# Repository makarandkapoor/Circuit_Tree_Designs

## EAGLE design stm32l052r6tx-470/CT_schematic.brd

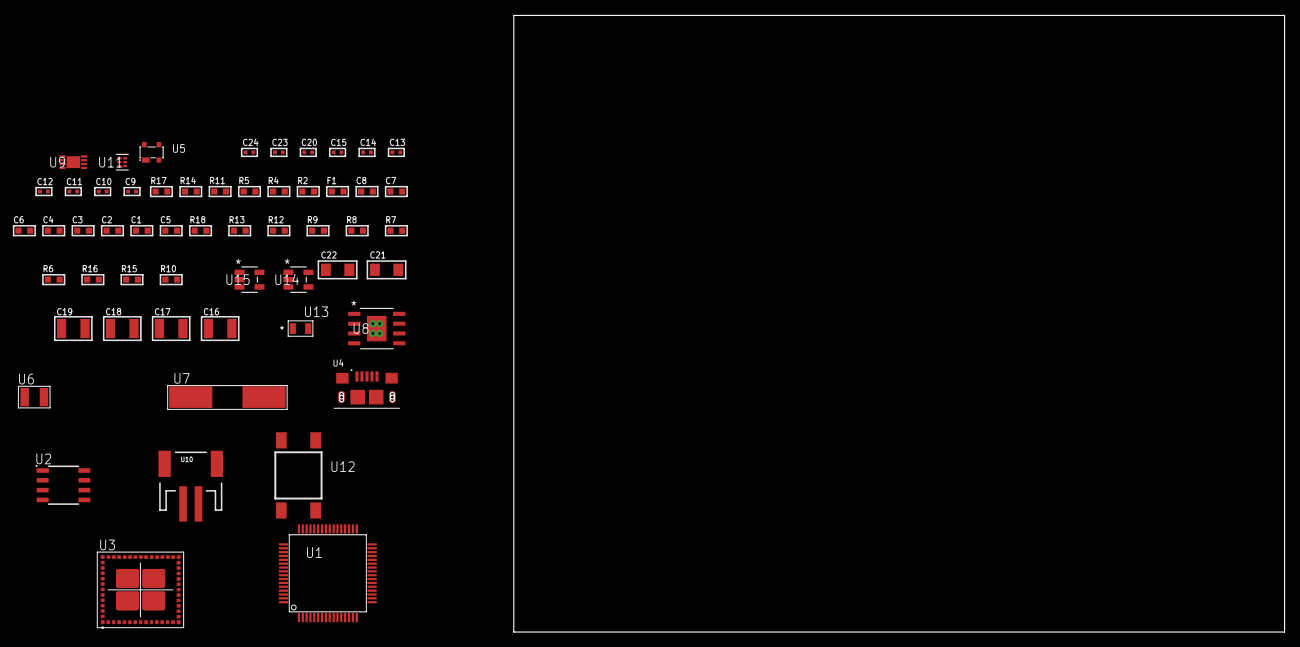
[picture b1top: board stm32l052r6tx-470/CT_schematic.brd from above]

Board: 2 copper layers, 122.6 x 80.0 mm, 56 parts (0 on the bottom side), 32 nets, no tracks yet.

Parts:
C1, C2, C3, C4, C8: 1e-07; C0603
C5: 4.7e-06; C0603
C6: 1e-08; C0603
C7: 1e-06; C0603
C9, C10, C11, C12: 1e-11; C0402
C13, C23, C24: 1e-08; C0402
C14, C15, C20: 1e-07; C0402
C16, C17, C18, C19: 1e-05; C1210
C21, C22: 1e-05; C1206
F1: 240.0; L0603
R2: 1000.0; R0603
R4, R5: 4700.0; R0603
R6, R7, R8, R9, R12, R13, R18: 10000.0; R0603
R10: 4031.5447154472; R0603
R11: 2200.0; R0603
R14: 9100.0; R0603
R15: 680000.0; R0603
R16: 120000.0; R0603
R17: 2000.0; R0603
U1: STM32L052R6T6; LQFP64
U2: AT25640B-SSHL-T; SOIC-8
U3: MBH7BLZ02-109004
U4: 10118193-0001LF; FCI_10118193-0001LF
U5: prtr5v0u2ax; SOT143B
U6: ABS07-32.768KHZ-7-T
U7: ABLS-25.000MHZ-B2F-T
U8: MIC5234YME; SOIC-8_EP
U9: MCP73831T-2ACI/MC; DFN8_2X3MC
U10: S2B-PH-SM4-TB(LF)(SN); JST-2-SMD
U11: TPS3895ADRYR; SON-6
U12: 4-1437565-2; SW_4-1437565-2
U13: Q65110A2395; LGM67K-G1J2-24-Z
U14, U15: nc7sz125m5x; NC7SZ125M5X

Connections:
CLK_CRYSTAL_U1_3: C9.1, U1.3, U6.1
CLK_CRYSTAL_U1_4: C10.1, U1.4, U6.2
CLK_CRYSTAL_U1_5: C11.1, U1.5, U7.1
CLK_CRYSTAL_U1_6: C12.1, U1.6, U7.2
GND: C1.2, C2.2, C3.2, C4.2, C5.2, C6.2, C7.2, C8.2, C9.2, C10.2, C11.2, C12.2, C13.2, C14.2, C15.2, C16.2, C17.2, C18.2, C19.2, C20.2, C21.2, C22.2, C23.2, C24.2, R2.2, R6.2, R11.2, R14.2, R16.2, R17.2, U1.12, U1.18, U1.31, U1.47, U1.63, U2.4, U3.1, U3.3, U3.15, U3.27, U3.29, U3.41, U3.42, U3.43, U3.44, U3.45, U3.46, U3.47, U3.48, U3.49, U3.50, U3.52, U3.53, U3.54, U3.55, U3.56, U4.5, U4.6, U4.7, U4.8, U4.9, U5.1, U8.7, U8.EPAD, U9.6, U9.9, U10.2, U11.2, U13.C, U14.1, U14.3, U15.1, U15.3
INPUT_USBPOWER_5V: C21.1, R18.2, U4.1, U5.4, U9.1, U9.2
NET_U1_7: R5.1, U1.7, U15.4
NET_U1_13: C6.1, C7.1, F1.1, U1.13
NET_U1_60: R6.1, U1.60
NET_U1_62: U12.3, U12.4
NET_U2_3: R7.1, U2.3
NET_U2_7: R9.1, U2.7
NET_U3_39: R4.1, U3.39, U14.4
NET_U8_4: R10.2, R11.1, U8.4
NET_U9_5: R18.1, U9.5
NET_U9_8: R17.1, U9.8
NET_U11_1: R13.1, R14.1, U11.1
NET_U11_3: R15.2, R16.1, U11.3
NET_U11_4: R12.1, U11.4, U14.2, U15.2
NET_U12_1: R2.1, U12.1, U12.2
PROC_LPUART1_CTS: U1.22, U3.26
PROC_LPUART1_RTS: U1.27, U3.24
PROC_LPUART1_RX: U1.25, U3.25
PROC_LPUART1_TX: U1.24, U3.23
PROC_SPI1_MISO: U1.56, U2.2
PROC_SPI1_MOSI: U1.23, U2.5
PROC_SPI1_NSS: R8.1, U1.20, U2.1
PROC_SPI1_SCK: U1.21, U2.6
PROC_USB_DM: U4.2, U5.3
PROC_USB_DP: U4.3, U5.2
VCC_S1_3V7: C16.1, C17.1, C22.1, U8.5, U8.8, U9.3, U9.4, U10.1
VCC_TIER1_3V3: C1.1, C2.1, C3.1, C4.1, C5.1, C8.1, C13.1, C14.1, C15.1, C18.1, C19.1, C20.1, C23.1, C24.1, F1.2, R4.2, R5.2, R7.2, R8.2, R9.2, R10.1, R12.2, R13.2, R15.1, U1.1, U1.19, U1.32, U1.48, U1.64, U2.8, U3.28, U8.1, U11.6, U14.5, U15.5

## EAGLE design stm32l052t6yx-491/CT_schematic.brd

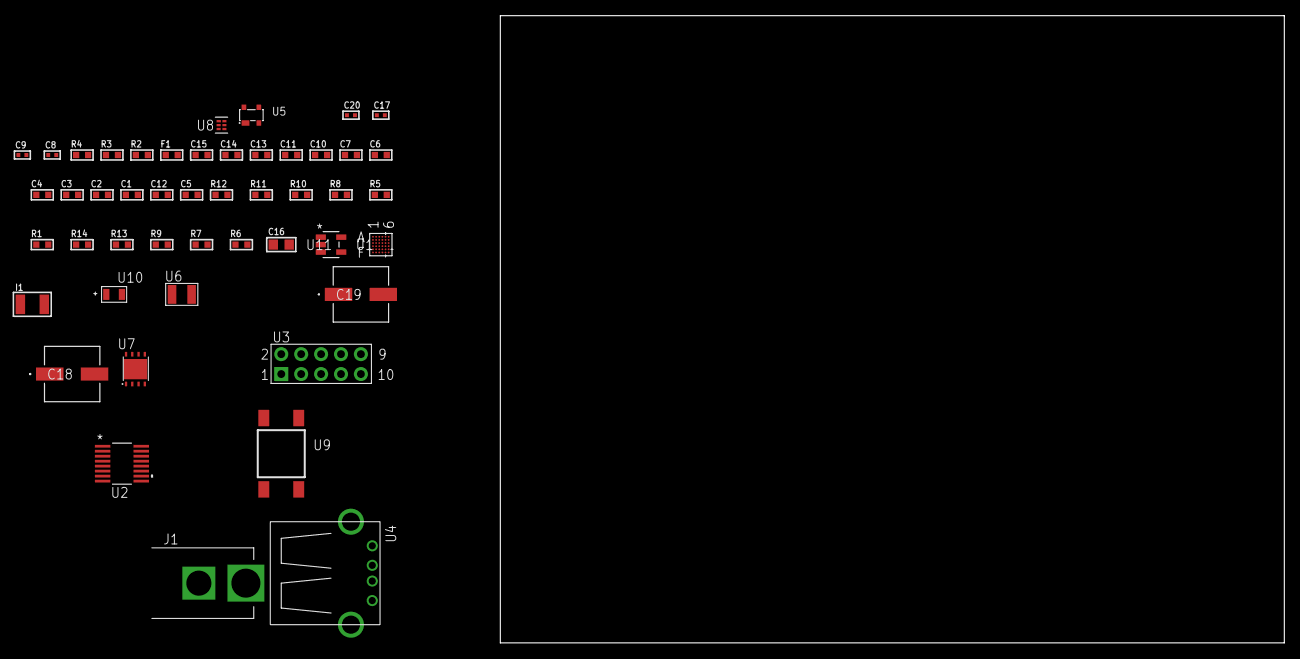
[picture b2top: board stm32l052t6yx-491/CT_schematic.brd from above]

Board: 2 copper layers, 100.0 x 80.0 mm, 48 parts (0 on the bottom side), 32 nets, no tracks yet.

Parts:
C1, C2, C3, C4: 1e-07; C0603
C5: 4.7e-06; C0603
C6: 1e-08; C0603
C7, C10, C11, C13, C14: 1e-06; C0603
C8, C9: 1e-11; C0402
C12: 2.2e-07; C0603
C15: 8e-07; R0603
C16: 1e-05; C0805
C17: 1e-07; C0402
C18, C19: 0.0001; EXV-9H
C20: 1e-08; C0402
F1: 240.0; L0603
I1: 1e-05; L1210
J1: PJ-037B; PJ-037B_PACKAGE
R1, R5, R10, R11: 10000.0; R0603
R2: 1000.0; R0603
R3: 910.0; R0603
R4: 4700.0; R0603
R6, R7, R9: 100000.0; R0603
R8: 36000.0; R0603
R12: 82000.0; R0603
R13: 300000.0; R0603
R14: 120000.0; R0603
U1: STM32L052T6Y6TR; WLCSP36
U2: LTC2804CGN-1#PBF; SSOP-16
U3: HTSS-105-01-G-D
U4: 61400416021; USB-A-H
U5: prtr5v0u2ax; SOT143B
U6: ABS07-32.768KHZ-7-T
U7: LP2951ACSDX/NOPB; WSON-8
U8: TPS3895ADRYR; SON-6
U9: 4-1437565-2; SW_4-1437565-2
U10: Q65110A2395; LGM67K-G1J2-24-Z
U11: nc7sz125m5x; NC7SZ125M5X

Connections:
CLK_CRYSTAL_U1_A6: C8.1, U1.A6, U6.1
CLK_CRYSTAL_U1_B6: C9.1, U1.B6, U6.2
GND: C1.2, C2.2, C3.2, C4.2, C5.2, C6.2, C7.2, C8.2, C9.2, C10.2, C11.2, C13.2, C14.2, C15.2, C16.2, C17.2, C18.2, C19.2, C20.2, J1.2, R2.2, R5.2, R9.2, R12.2, R14.2, U1.D6, U2.8, U3.9, U4.4, U4.5, U4.6, U5.1, U7.3, U7.4, U7.PAD, U8.2, U10.C, U11.1, U11.3
NET_U1_C5: R5.1, U1.C5
NET_U1_C6: R4.1, U1.C6, U11.4
NET_U1_D5: C6.1, C7.1, F1.1, U1.D5, U1.E6
NET_U1_F5: R3.1, U1.F5, U10.A
NET_U1_F6: R1.1, U1.F6, U9.3, U9.4
NET_U2_6: C10.1, U2.6
NET_U2_7: C12.1, I1.2, U2.7
NET_U2_9: C11.1, U2.9
NET_U2_10: C12.2, U2.10
NET_U2_11: R6.1, U2.11
NET_U3_3: U2.1, U3.3
NET_U3_4: U2.2, U3.4
NET_U3_5: U2.3, U3.5
NET_U3_6: U2.4, U3.6
NET_U5_4: U4.1, U5.4
NET_U7_5: R7.1, U7.5
NET_U7_7: R8.2, R9.1, U7.7
NET_U8_1: R11.1, R12.1, U8.1
NET_U8_3: R13.2, R14.1, U8.3
NET_U8_4: R10.1, U8.4, U11.2
NET_U9_1: R2.1, U9.1, U9.2
PROC_LPUART1_CTS: U1.E3, U2.13
PROC_LPUART1_RTS: U1.C3, U2.15
PROC_LPUART1_RX: U1.D2, U2.16
PROC_LPUART1_TX: U1.E2, U2.14
PROC_USB_DM: U1.C2, U4.2, U5.3
PROC_USB_DP: U1.B1, U4.3, U5.2
VCC_S1_11V7: C15.1, C18.1, C19.1, J1.1, U7.8
VCC_TIER1_1V8: C1.1, C2.1, C3.1, C4.1, C5.1, C13.1, C14.1, C16.1, C17.1, C20.1, F1.2, I1.1, R1.2, R3.2, R4.2, R6.2, R7.2, R8.1, R10.2, R11.2, R13.1, U1.A5, U1.F1, U2.5, U2.12, U7.1, U8.6, U11.5

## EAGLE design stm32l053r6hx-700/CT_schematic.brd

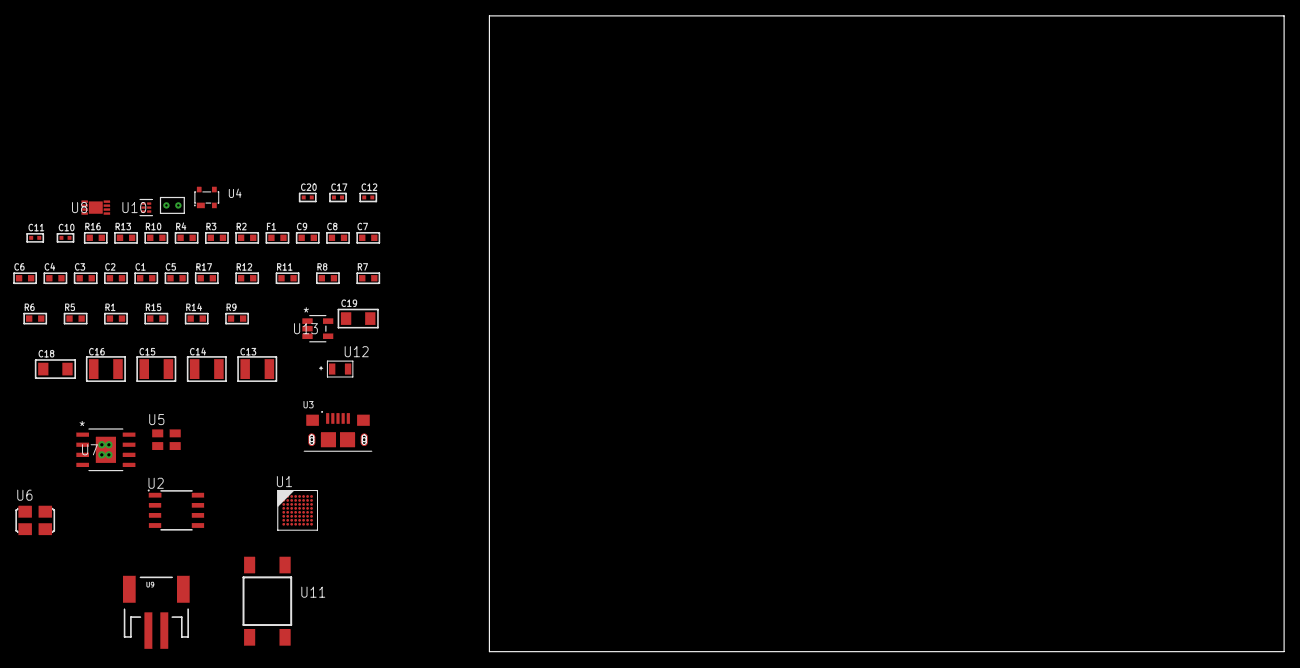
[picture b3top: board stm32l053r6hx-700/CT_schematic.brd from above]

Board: 2 copper layers, 122.6 x 80.0 mm, 52 parts (0 on the bottom side), 28 nets, no tracks yet.

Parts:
C1, C2, C3, C4, C6, C9: 1e-07; C0603
C5: 4.7e-06; C0603
C7: 1e-08; C0603
C8: 1e-06; C0603
C10, C11, C12, C20: 1e-08; C0402
C13, C14, C15, C16: 1e-05; C1210
C17: 1e-07; C0402
C18, C19: 1e-05; C1206
F1: 240.0; L0603
R1, R5, R6, R7, R8, R11, R12, R17: 10000.0; R0603
R2: 1000.0; R0603
R3: 1600.5; R0603
R4: 4700.0; R0603
R9: 4031.5447154472; R0603
R10: 2200.0; R0603
R13: 9100.0; R0603
R14: 680000.0; R0603
R15: 120000.0; R0603
R16: 2000.0; R0603
U1: STM32L053R6H6; TFBGA64
U2: AT25010B-SSHL-T; SOIC-8
U3: 10118193-0001LF; FCI_10118193-0001LF
U4: prtr5v0u2ax; SOT143B
U5: ASEK-32.768KHz-ECST; ASEK
U6: ASFL1-25MHZ-NCS; ASFL1
U7: MIC5234YME; SOIC-8_EP
U8: MCP73831T-2ACI/MC; DFN8_2X3MC
U9: S2B-PH-SM4-TB(LF)(SN); JST-2-SMD
U10: TPS3895ADRYR; SON-6
U11: 4-1437565-2; SW_4-1437565-2
U12: Q65110A2395; LGM67K-G1J2-24-Z
U13: nc7sz125m5x; NC7SZ125M5X
U14: Dummy; DUMMY_PACKAGE_116

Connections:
CLK_U1_A1: U1.A1, U5.3
CLK_U1_C1: U1.C1, U6.3
GND: C1.2, C2.2, C3.2, C4.2, C5.2, C6.2, C7.2, C8.2, C9.2, C10.2, C11.2, C12.2, C13.2, C14.2, C15.2, C16.2, C17.2, C18.2, C19.2, C20.2, R2.2, R5.2, R10.2, R13.2, R15.2, R16.2, U1.C2, U1.D4, U1.D5, U1.D6, U1.F1, U2.4, U3.5, U3.6, U3.7, U3.8, U3.9, U4.1, U5.2, U6.2, U7.7, U7.EPAD, U8.6, U8.9, U9.2, U10.2, U12.C, U13.1, U13.3, U14.1
INPUT_USBPOWER_5V: C18.1, R17.2, U3.1, U4.4, U8.1, U8.2
NET_U1_B2: C6.1, U1.B2
NET_U1_B4: R5.1, U1.B4
NET_U1_E1: R4.1, U1.E1, U13.4
NET_U1_H1: C7.1, C8.1, F1.1, U1.G1, U1.H1
NET_U1_H7: R3.1, U1.H7, U12.A
NET_U1_H8: R1.1, U1.H8, U11.3, U11.4
NET_U2_3: R6.1, U2.3
NET_U2_7: R8.1, U2.7
NET_U7_4: R9.2, R10.1, U7.4
NET_U8_5: R17.1, U8.5
NET_U8_8: R16.1, U8.8
NET_U10_1: R12.1, R13.1, U10.1
NET_U10_3: R14.2, R15.1, U10.3
NET_U10_4: R11.1, U10.4, U13.2
NET_U11_1: R2.1, U11.1, U11.2
PROC_DAC_OUT1: U1.H3, U14.2
PROC_SPI1_MISO: U1.A4, U2.2
PROC_SPI1_MOSI: U1.C4, U2.5
PROC_SPI1_NSS: R7.1, U1.A6, U2.1
PROC_SPI1_SCK: U1.A5, U2.6
PROC_USB_DM: U1.C8, U3.2, U4.3
PROC_USB_DP: U1.B8, U3.3, U4.2
VCC_S1_3V7: C13.1, C14.1, C19.1, U7.5, U7.8, U8.3, U8.4, U9.1
VCC_TIER1_3V3: C1.1, C2.1, C3.1, C4.1, C5.1, C9.1, C10.1, C11.1, C12.1, C15.1, C16.1, C17.1, C20.1, F1.2, R1.2, R3.2, R4.2, R6.2, R7.2, R8.2, R9.1, R11.2, R12.2, R14.1, U1.D2, U1.E4, U1.E5, U1.E6, U2.8, U5.4, U6.4, U7.1, U10.6, U13.5

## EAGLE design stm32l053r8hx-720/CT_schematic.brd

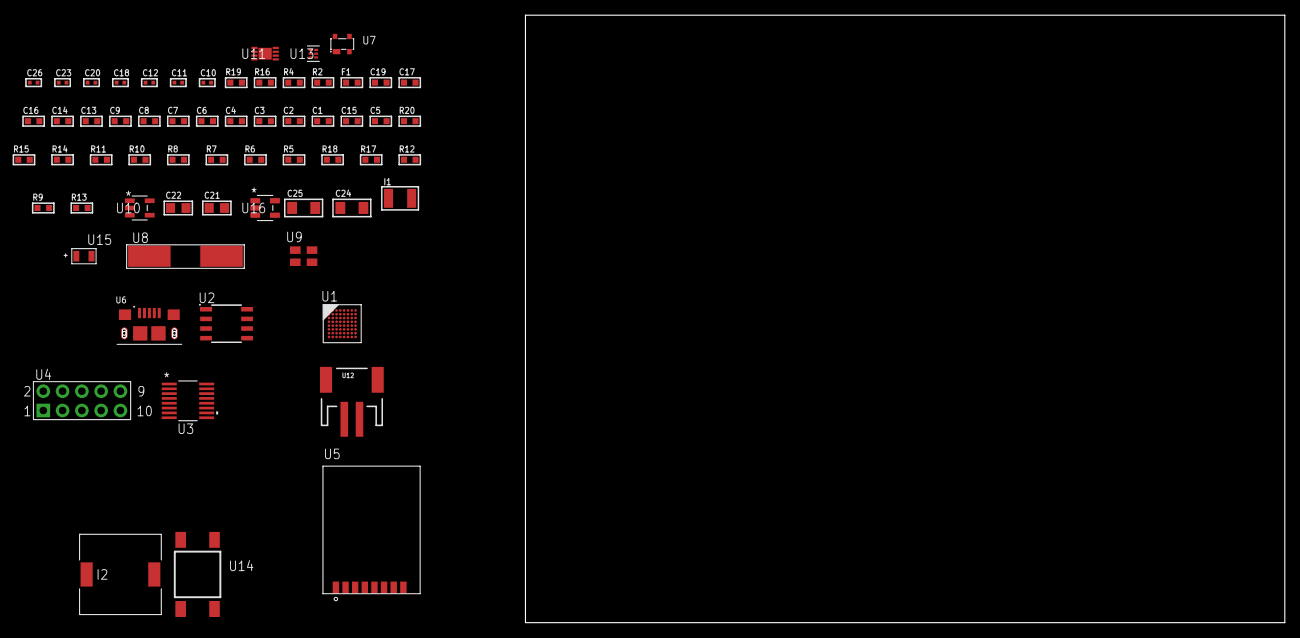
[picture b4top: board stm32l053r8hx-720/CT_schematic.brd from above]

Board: 2 copper layers, 63 parts (0 on the bottom side), 47 nets, no tracks yet.

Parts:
C1, C2, C3, C4, C6, C9: 1e-07; C0603
C5: 4.7e-06; C0603
C7: 1e-08; C0603
C8, C13, C14, C16, C17, C19: 1e-06; C0603
C10, C11: 1e-11; C0402
C12, C20, C26: 1e-08; C0402
C15: 2.2e-07; C0603
C18, C23: 1e-07; C0402
C21, C22: 1e-05; C0805
C24, C25: 1e-05; C1206
F1: 240.0; L0603
I1: 1e-05; L1210
I2: 5.2e-06; DR1040
R2: 1000.0; R0603
R4: 4700.0; R0603
R5, R6, R7, R8, R10, R11, R14, R15, R20: 10000.0; R0603
R9: 100000.0; R0603
R12: 220000.0; R0603
R13: 1000000.0; R0603
R16: 9100.0; R0603
R17: 680000.0; R0603
R18: 120000.0; R0603
R19: 2000.0; R0603
U1: STM32L053R8H6; TFBGA64
U2: AT25080B-SSHL-T; SOIC-8
U3: LTC2804CGN-1#PBF; SSOP-16
U4: HTSS-105-01-G-D
U5: RFM75-S
U6: 10118193-0001LF; FCI_10118193-0001LF
U7: prtr5v0u2ax; SOT143B
U8: ABLS-25.000MHZ-B2F-T
U9: ASEK-32.768KHz-ECST; ASEK
U10: ltc3406es5; TSOT-23-5
U11: MCP73831T-2ACI/MC; DFN8_2X3MC
U12: S2B-PH-SM4-TB(LF)(SN); JST-2-SMD
U13: TPS3895ADRYR; SON-6
U14: 4-1437565-2; SW_4-1437565-2
U15: Q65110A2395; LGM67K-G1J2-24-Z
U16: nc7sz125m5x; NC7SZ125M5X

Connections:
CLK_CRYSTAL_U1_C1: C10.1, U1.C1, U8.1
CLK_CRYSTAL_U1_D1: C11.1, U1.D1, U8.2
CLK_U1_A1: U1.A1, U9.3
GND: C1.2, C2.2, C3.2, C4.2, C5.2, C6.2, C7.2, C8.2, C9.2, C10.2, C11.2, C12.2, C13.2, C14.2, C16.2, C17.2, C18.2, C19.2, C20.2, C21.2, C22.1, C22.2, C23.2, C24.2, C25.2, C26.2, R2.2, R5.2, R12.2, R16.2, R18.2, R19.2, U1.C2, U1.D4, U1.D5, U1.D6, U1.F1, U2.4, U3.8, U4.9, U5.1, U6.5, U6.6, U6.7, U6.8, U6.9, U7.1, U9.2, U10.2, U11.6, U11.9, U12.2, U13.2, U15.C, U16.1, U16.3
INPUT_USBPOWER_5V: C24.1, R20.2, U6.1, U7.4, U11.1, U11.2
NET_U1_B2: C6.1, U1.B2
NET_U1_B4: R5.1, U1.B4
NET_U1_E1: R4.1, U1.E1, U16.4
NET_U1_H1: C7.1, C8.1, F1.1, U1.G1, U1.H1
NET_U1_H8: U14.3, U14.4
NET_U2_3: R6.1, U2.3
NET_U2_7: R8.1, U2.7
NET_U3_6: C13.1, U3.6
NET_U3_7: C15.1, I1.2, U3.7
NET_U3_9: C14.1, U3.9
NET_U3_10: C15.2, U3.10
NET_U3_11: R9.1, U3.11
NET_U4_3: U3.1, U4.3
NET_U4_4: U3.2, U4.4
NET_U4_5: U3.3, U4.5
NET_U4_6: U3.4, U4.6
NET_U5_3: R10.1, U5.3
NET_U10_3: I2.1, U10.3
NET_U10_5: R12.1, R13.1, U10.5
NET_U10_ATNET_3: I2.2, R13.2
NET_U11_5: R20.1, U11.5
NET_U11_8: R19.1, U11.8
NET_U13_1: R15.1, R16.1, U13.1
NET_U13_3: R17.2, R18.1, U13.3
NET_U13_4: R14.1, U13.4, U16.2
NET_U14_1: R2.1, U14.1, U14.2
PROC_LPUART1_CTS: U1.G4, U3.13
PROC_LPUART1_RTS: U1.B5, U3.15
PROC_LPUART1_RX: U1.B6, U3.16
PROC_LPUART1_TX: U1.B7, U3.14
PROC_SPI1_MISO: U1.A4, U5.7
PROC_SPI1_MOSI: U1.C4, U5.6
PROC_SPI1_NSS: R11.1, U1.A6, U5.4
PROC_SPI1_SCK: U1.A5, U5.5
PROC_SPI2_MISO: U1.F2, U2.2
PROC_SPI2_MOSI: U1.F7, U2.5
PROC_SPI2_NSS: R7.1, U1.A3, U2.1
PROC_SPI2_SCK: U1.G7, U2.6
PROC_USB_DM: U1.C8, U6.2, U7.3
PROC_USB_DP: U1.B8, U6.3, U7.2
VCC_S1_3V7: C21.1, C25.1, U10.4, U11.3, U11.4, U12.1
VCC_TIER1_3V3: C1.1, C2.1, C3.1, C4.1, C5.1, C9.1, C12.1, C16.1, C17.1, C18.1, C19.1, C20.1, C22.2, C23.1, C26.1, F1.2, I1.1, I2.2, R4.2, R6.2, R7.2, R8.2, R9.2, R10.2, R11.2, R13.2, R14.2, R15.2, R17.1, U1.D2, U1.E4, U1.E5, U1.E6, U2.8, U3.5, U3.12, U5.2, U9.4, U13.6, U16.5

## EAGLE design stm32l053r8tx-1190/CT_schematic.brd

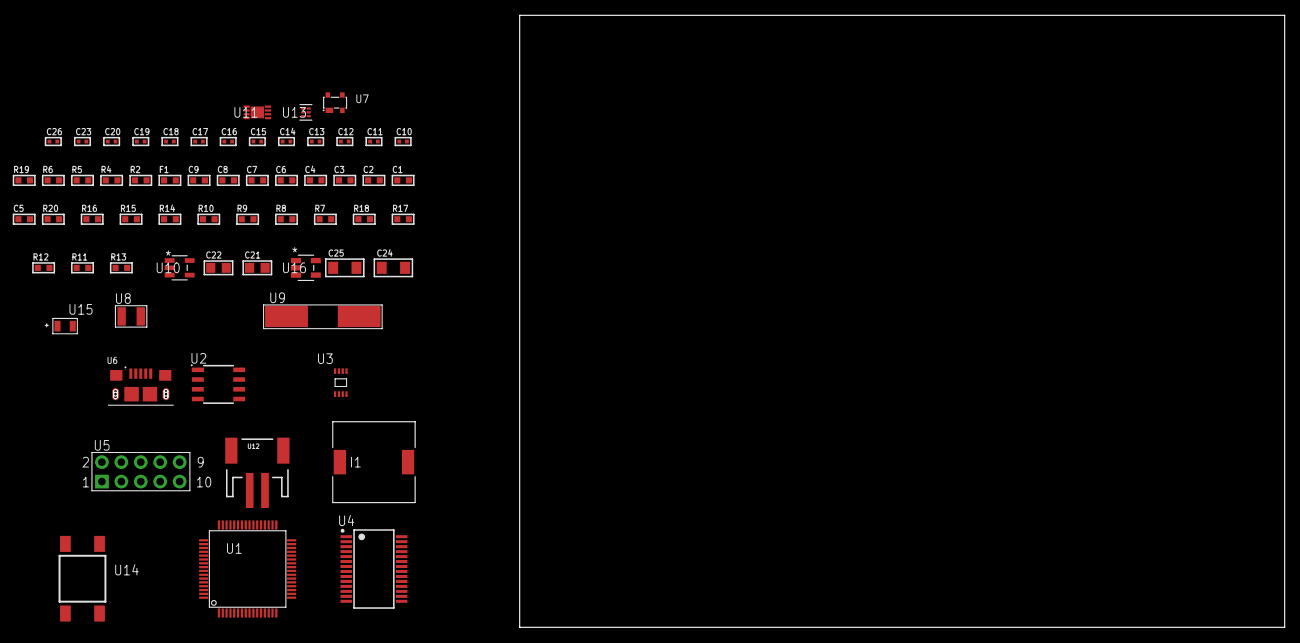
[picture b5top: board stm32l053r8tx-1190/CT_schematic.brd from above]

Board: 2 copper layers, 153.1 x 80.0 mm, 62 parts (0 on the bottom side), 47 nets, no tracks yet.

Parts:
C1, C2, C3, C4, C6, C9: 1e-07; C0603
C5: 4.7e-06; C0603
C7: 1e-08; C0603
C8: 1e-06; C0603
C10, C11, C12, C13: 1e-11; C0402
C14, C15, C26: 1e-08; C0402
C16, C17, C18, C19, C20, C23: 1e-07; C0402
C21, C22: 1e-05; C0805
C24, C25: 1e-05; C1206
F1: 240.0; L0603
I1: 7e-06; DR1040
R2: 1000.0; R0603
R4: 4700.0; R0603
R5, R6: 2200.0; R0603
R7, R8, R9, R10, R14, R15, R20: 10000.0; R0603
R11: 100000.0; R0603
R12: 245000.0; R0603
R13: 1000000.0; R0603
R16: 11000.0; R0603
R17: 620000.0; R0603
R18: 120000.0; R0603
R19: 2000.0; R0603
U1: STM32L053R8T3; LQFP64
U2: AT25M02-SSHD-T; SOIC-8
U3: 24AA02T-I/MNY; TDFN-8/6MM
U4: ST3241EBPR; SSOP-28
U5: HTSS-105-01-G-D
U6: 10118193-0001LF; FCI_10118193-0001LF
U7: prtr5v0u2ax; SOT143B
U8: ABS07-32.768KHZ-7-T
U9: ABLS-25.000MHZ-B2F-T
U10: ltc3406es5; TSOT-23-5
U11: MCP73831T-2ACI/MC; DFN8_2X3MC
U12: S2B-PH-SM4-TB(LF)(SN); JST-2-SMD
U13: TPS3895ADRYR; SON-6
U14: 4-1437565-2; SW_4-1437565-2
U15: Q65110A2395; LGM67K-G1J2-24-Z
U16: nc7sz125m5x; NC7SZ125M5X

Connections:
CLK_CRYSTAL_U1_3: C10.1, U1.3, U8.1
CLK_CRYSTAL_U1_4: C11.1, U1.4, U8.2
CLK_CRYSTAL_U1_5: C12.1, U1.5, U9.1
CLK_CRYSTAL_U1_6: C13.1, U1.6, U9.2
GND: C1.2, C2.2, C3.2, C4.2, C5.2, C6.2, C7.2, C8.2, C9.2, C10.2, C11.2, C12.2, C13.2, C14.2, C15.2, C16.2, C19.2, C20.2, C21.2, C22.1, C22.2, C23.2, C24.2, C25.2, C26.2, R2.2, R7.2, R12.2, R16.2, R18.2, R19.2, U1.12, U1.18, U1.31, U1.47, U1.63, U2.4, U3.4, U4.23, U4.25, U5.9, U6.5, U6.6, U6.7, U6.8, U6.9, U7.1, U10.2, U11.6, U11.9, U12.2, U13.2, U15.C, U16.1, U16.3
INPUT_USBPOWER_5V: C24.1, R20.2, U6.1, U7.4, U11.1, U11.2
NET_U1_1: C6.1, U1.1
NET_U1_7: R4.1, U1.7, U16.4
NET_U1_13: C7.1, C8.1, F1.1, U1.13
NET_U1_58: R5.1, U1.58, U3.6
NET_U1_59: R6.1, U1.59, U3.5
NET_U1_60: R7.1, U1.60
NET_U1_62: U14.3, U14.4
NET_U2_3: R8.1, U2.3
NET_U2_7: R10.1, U2.7
NET_U4_1: C18.1, U4.1
NET_U4_2: C18.2, U4.2
NET_U4_3: C20.1, U4.3
NET_U4_22: R11.1, U4.22
NET_U4_24: C17.2, U4.24
NET_U4_27: C19.1, U4.27
NET_U4_28: C17.1, U4.28
NET_U5_3: U4.4, U5.3
NET_U5_4: U4.5, U5.4
NET_U5_5: U4.9, U5.5
NET_U5_6: U4.10, U5.6
NET_U10_3: I1.1, U10.3
NET_U10_5: R12.1, R13.1, U10.5
NET_U10_ATNET_3: I1.2, R13.2
NET_U11_5: R20.1, U11.5
NET_U11_8: R19.1, U11.8
NET_U13_1: R15.1, R16.1, U13.1
NET_U13_3: R17.2, R18.1, U13.3
NET_U13_4: R14.1, U13.4, U16.2
NET_U14_1: R2.1, U14.1, U14.2
PROC_LPUART1_CTS: U1.22, U4.13
PROC_LPUART1_RTS: U1.27, U4.18
PROC_LPUART1_RX: U1.25, U4.19
PROC_LPUART1_TX: U1.24, U4.14
PROC_SPI1_MISO: U1.56, U2.2
PROC_SPI1_MOSI: U1.23, U2.5
PROC_SPI1_NSS: R9.1, U1.20, U2.1
PROC_SPI1_SCK: U1.21, U2.6
PROC_USB_DM: U1.44, U6.2, U7.3
PROC_USB_DP: U1.45, U6.3, U7.2
VCC_S1_3V7: C21.1, C25.1, U10.4, U11.3, U11.4, U12.1
VCC_TIER1_3V0: C1.1, C2.1, C3.1, C4.1, C5.1, C9.1, C14.1, C15.1, C16.1, C22.2, C23.1, C26.1, F1.2, I1.2, R4.2, R5.2, R6.2, R8.2, R9.2, R10.2, R11.2, R13.2, R14.2, R15.2, R17.1, U1.19, U1.32, U1.48, U1.64, U2.8, U3.7, U3.8, U4.26, U13.6, U16.5

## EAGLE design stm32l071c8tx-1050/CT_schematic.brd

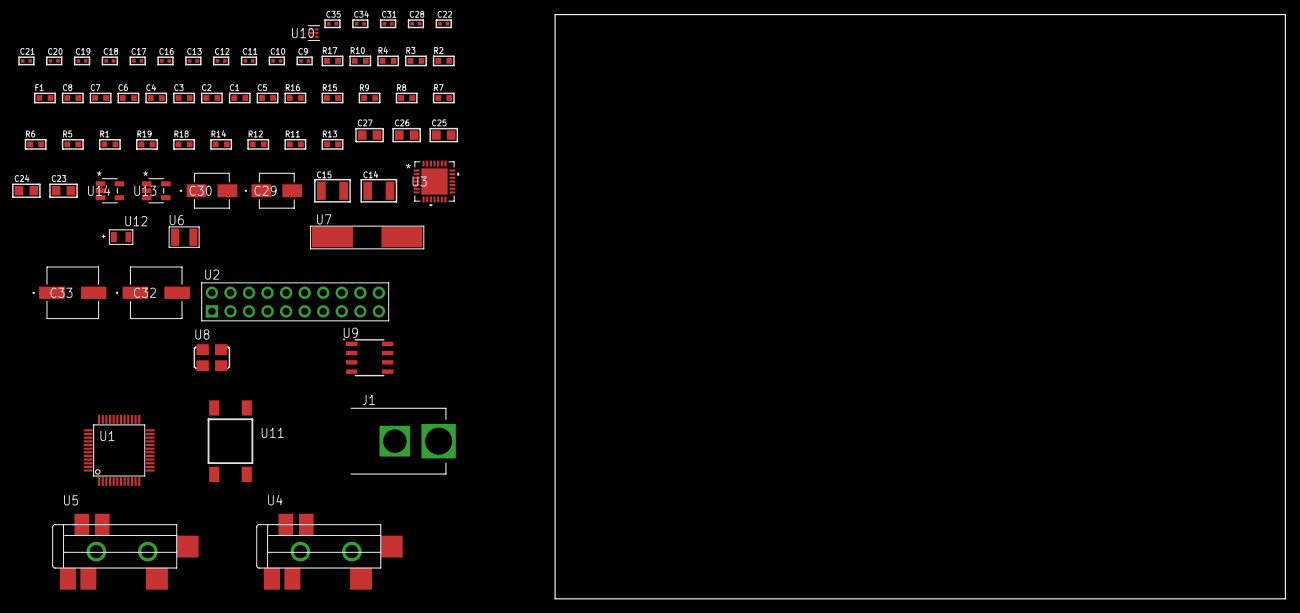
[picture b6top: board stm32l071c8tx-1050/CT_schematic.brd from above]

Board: 2 copper layers, 100.0 x 80.0 mm, 70 parts (0 on the bottom side), 30 nets, no tracks yet.

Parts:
C1, C2, C3, C4, C6: 1e-07; C0603
C5: 4.7e-06; C0603
C7: 1e-08; C0603
C8: 1e-06; C0603
C9, C10, C11, C12: 1e-11; C0402
C13, C18, C19, C20, C21, C22, C31: 1e-07; C0402
C14, C15: 2.2e-05; C1210
C16, C17: 1e-09; C0402
C23, C24, C25, C26, C27: 1e-05; C0805
C28, C34, C35: 1e-08; C0402
C29: 1e-06; EXV-9B
C30: 2.2e-06; EXV-9B
C32, C33: 0.0001; EXV-9H
F1: 240.0; L0603
J1: PJ-037B; PJ-037B_PACKAGE
R1, R5, R6, R15, R16: 10000.0; R0603
R2: 1000.0; R0603
R3: 1600.5; R0603
R4: 4700.0; R0603
R7, R8, R9: 47000.0; R0603
R10: 680.0; R0603
R11, R12, R14: 100000.0; R0603
R13: 164658.62; R0603
R17: 9100.0; R0603
R18: 680000.0; R0603
R19: 120000.0; R0603
U1: STM32L071C8T7; LQFP48
U2: TST-110-05-T-D-RA
U3: WM8731CLSEFL; QFN-28
U4, U5: SJ-43515TS-SMT-TR
U6: ABS07-32.768KHZ-7-T
U7: ABLS-25.000MHZ-B2F-T
U8: ASFL1-12.288MHZ-EC-T; ASFL1
U9: LP2954AIMX/NOPB; LP2954
U10: TPS3895ADRYR; SON-6
U11: 4-1437565-2; SW_4-1437565-2
U12: Q65110A2395; LGM67K-G1J2-24-Z
U13, U14: nc7sz125m5x; NC7SZ125M5X

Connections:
CLK_CRYSTAL_U1_3: C9.1, U1.3, U6.1
CLK_CRYSTAL_U1_4: C10.1, U1.4, U6.2
CLK_CRYSTAL_U1_5: C11.1, U1.5, U7.1
CLK_CRYSTAL_U1_6: C12.1, U1.6, U7.2
CLK_U3_1: U3.1, U8.3
GND: C1.2, C2.2, C3.2, C4.2, C5.2, C6.2, C7.2, C8.2, C9.2, C10.2, C11.2, C12.2, C13.2, C17.2, C18.2, C19.2, C20.2, C21.2, C22.2, C23.2, C24.2, C25.2, C26.2, C27.2, C28.2, C29.2, C30.2, C31.2, C32.2, C33.2, C34.2, C35.2, J1.2, R2.2, R5.2, R7.2, R8.2, R9.2, R14.2, R17.2, R19.2, U1.8, U1.23, U1.35, U1.47, U2.4, U2.6, U2.8, U2.10, U2.12, U2.14, U2.16, U2.18, U2.20, U3.4, U3.15, U3.19, U3.25, U3.26, U3.29, U4.1, U5.1, U8.2, U9.4, U10.2, U12.C, U13.2, U13.3, U14.1, U14.3
NET_U1_7: R4.1, U1.7, U14.4
NET_U1_9: C7.1, C8.1, F1.1, U1.9
NET_U1_44: R5.1, U1.44
NET_U1_45: R3.1, U1.45, U12.A
NET_U1_46: R1.1, U1.46, U11.3, U11.4
NET_U3_20: C22.1, C27.1, U3.20
NET_U4_2: C15.1, R8.1, U4.2
NET_U4_5: C14.1, R7.1, U4.5
NET_U5_5: C16.1, C17.1, R9.1, R10.1, U5.5
NET_U9_3: R12.1, U9.3
NET_U9_5: R11.1, U9.5
NET_U9_7: R13.2, R14.1, U9.7
NET_U10_1: R16.1, R17.1, U10.1
NET_U10_3: R18.2, R19.1, U10.3
NET_U10_4: R15.1, U10.4, U13.4, U14.2
NET_U11_1: R2.1, U11.1, U11.2
PROC_I2S2_CK: U1.26, U3.7
PROC_I2S2_SD: U1.28, U3.8
PROC_I2S2_WS: U1.25, U3.9, U3.11
PROC_SYS_SWCLK: U1.37, U2.9
PROC_SYS_SWDIO: U1.34, U2.7
RST_OUT_U2_SRESET_B: R6.1, U2.15, U13.1
VCC_S1_11V3: C29.1, C32.1, C33.1, J1.1, R12.2, U9.8
VCC_TIER1_3V3: C1.1, C2.1, C3.1, C4.1, C5.1, C6.1, C13.1, C18.1, C19.1, C20.1, C21.1, C23.1, C24.1, C25.1, C26.1, C28.1, C30.1, C31.1, C34.1, C35.1, F1.2, R1.2, R3.2, R4.2, R6.2, R11.2, R13.1, R15.2, R16.2, R18.1, U1.1, U1.24, U1.36, U1.48, U2.1, U3.3, U3.5, U3.12, U3.18, U8.4, U9.1, U10.6, U13.5, U14.5

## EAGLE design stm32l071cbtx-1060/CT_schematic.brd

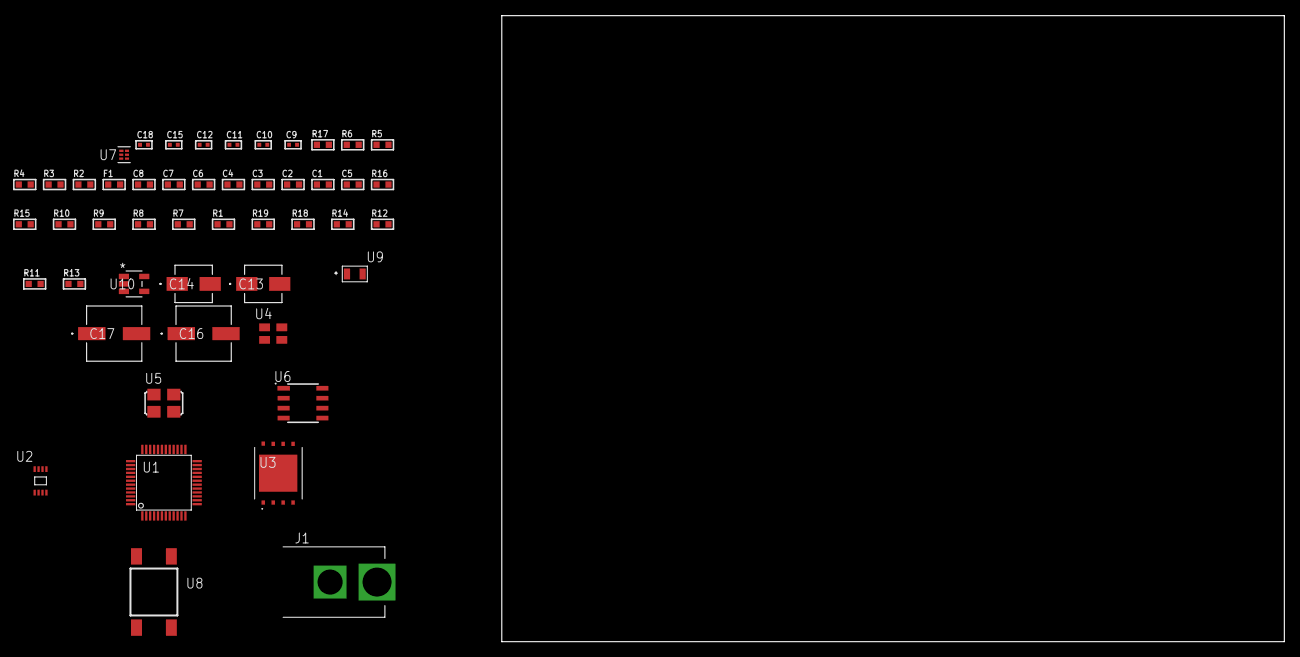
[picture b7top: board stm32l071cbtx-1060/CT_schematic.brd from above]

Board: 2 copper layers, 100.0 x 80.0 mm, 49 parts (0 on the bottom side), 25 nets, no tracks yet.

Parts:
C1, C2, C3, C4, C6: 1e-07; C0603
C5: 4.7e-06; C0603
C7: 1e-08; C0603
C8: 1e-06; C0603
C9, C10, C11, C12, C18: 1e-08; C0402
C13: 1e-06; EXV-9B
C14: 2.2e-06; EXV-9B
C15: 1e-07; C0402
C16, C17: 0.0001; EXV-9H
F1: 240.0; L0603
J1: PJ-037B; PJ-037B_PACKAGE
R1, R7, R8, R9, R10, R15, R16: 10000.0; R0603
R2: 1000.0; R0603
R3: 1600.5; R0603
R4: 4700.0; R0603
R5, R6: 2200.0; R0603
R11, R12, R14: 100000.0; R0603
R13: 164658.62; R0603
R17: 9100.0; R0603
R18: 680000.0; R0603
R19: 120000.0; R0603
U1: STM32L071CBT7; LQFP48
U2: 24AA08T-I/MNY; TDFN-8/6MM
U3: S25FL128SDPNFI001; WNG008
U4: ASEK-32.768KHz-ECST; ASEK
U5: ASFL1-25MHZ-NCS; ASFL1
U6: LP2954AIMX/NOPB; LP2954
U7: TPS3895ADRYR; SON-6
U8: 4-1437565-2; SW_4-1437565-2
U9: Q65110A2395; LGM67K-G1J2-24-Z
U10: nc7sz125m5x; NC7SZ125M5X

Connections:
CLK_U1_3: U1.3, U4.3
CLK_U1_5: U1.5, U5.3
GND: C1.2, C2.2, C3.2, C4.2, C5.2, C6.2, C7.2, C8.2, C9.2, C10.2, C11.2, C12.2, C13.2, C14.2, C15.2, C16.2, C17.2, C18.2, J1.2, R2.2, R7.2, R14.2, R17.2, R19.2, U1.8, U1.23, U1.35, U1.47, U2.4, U2.7, U3.4, U3.PAD, U4.2, U5.2, U6.4, U7.2, U9.C, U10.1, U10.3
NET_U1_7: R4.1, U1.7, U10.4
NET_U1_9: C7.1, C8.1, F1.1, U1.9
NET_U1_30: R5.1, U1.30, U2.6
NET_U1_31: R6.1, U1.31, U2.5
NET_U1_44: R7.1, U1.44
NET_U1_45: R3.1, U1.45, U9.A
NET_U1_46: R1.1, U1.46, U8.3, U8.4
NET_U3_3: R8.1, U3.3
NET_U3_7: R10.1, U3.7
NET_U6_3: R12.1, U6.3
NET_U6_5: R11.1, U6.5
NET_U6_7: R13.2, R14.1, U6.7
NET_U7_1: R16.1, R17.1, U7.1
NET_U7_3: R18.2, R19.1, U7.3
NET_U7_4: R15.1, U7.4, U10.2
NET_U8_1: R2.1, U8.1, U8.2
PROC_SPI1_MISO: U1.16, U3.2
PROC_SPI1_MOSI: U1.17, U3.5
PROC_SPI1_NSS: R9.1, U1.14, U3.1
PROC_SPI1_SCK: U1.15, U3.6
VCC_S1_7V8: C13.1, C16.1, C17.1, J1.1, R12.2, U6.8
VCC_TIER1_3V3: C1.1, C2.1, C3.1, C4.1, C5.1, C6.1, C9.1, C10.1, C11.1, C12.1, C14.1, C15.1, C18.1, F1.2, R1.2, R3.2, R4.2, R5.2, R6.2, R8.2, R9.2, R10.2, R11.2, R13.1, R15.2, R16.2, R18.1, U1.1, U1.24, U1.36, U1.48, U2.8, U3.8, U4.4, U5.4, U6.1, U7.6, U10.5
